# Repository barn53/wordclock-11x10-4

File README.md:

# wordclock-11x10-4
Wordclock project with 11x10 letter display + 4 minute identifier

# KiCad dependencies:

https://github.com/gerdmuller/barn53-kicad-library.git

https://github.com/Digi-Key/digikey-kicad-library.git

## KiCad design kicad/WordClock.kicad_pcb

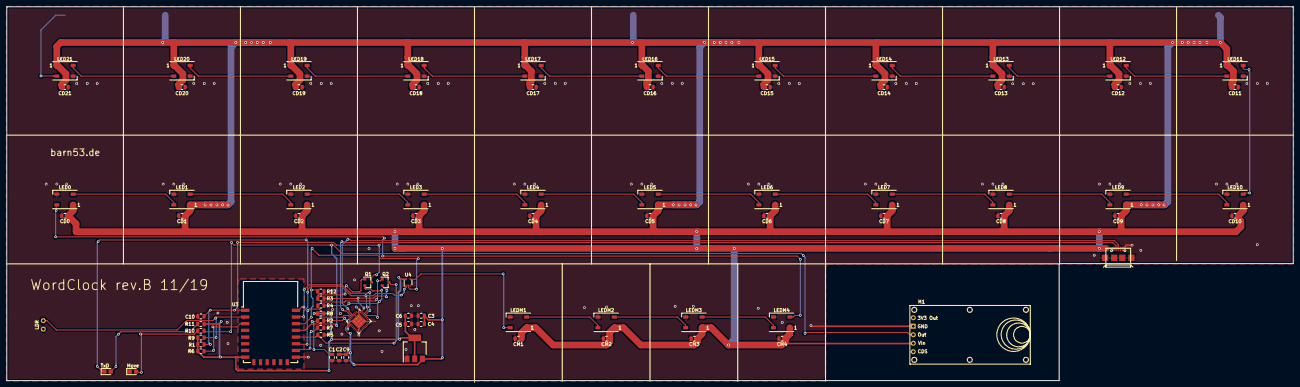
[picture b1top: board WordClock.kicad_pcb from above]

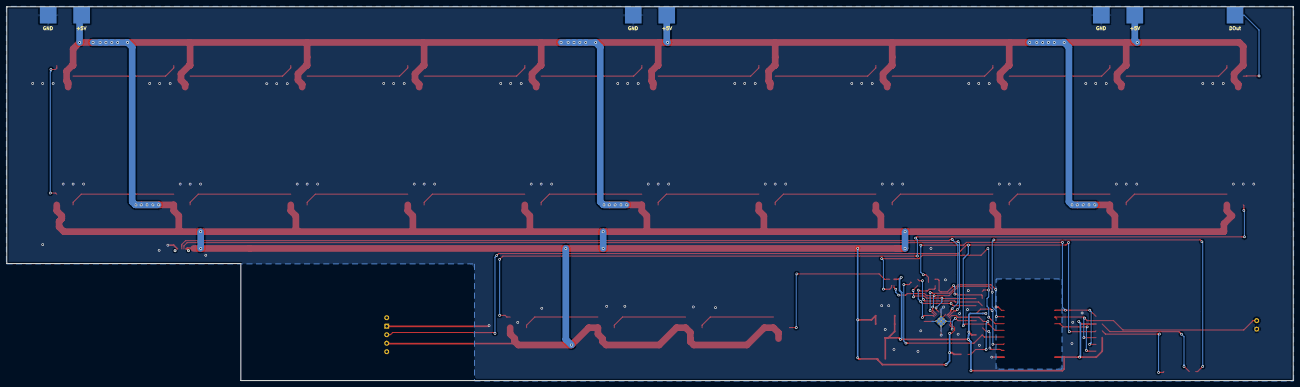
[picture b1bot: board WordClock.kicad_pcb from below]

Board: 2 copper layers, 384.8 x 111.8 mm, 90 parts (7 on the bottom side), 50 nets.

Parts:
C1, C4, C5, C9, C10: 100n; C_0805_2012Metric
C2: 4.7u; C_0805_2012Metric
C3, C6: 10u; C_0805_2012Metric
CD0, CD1, CD2, CD3, CD4, CD5, CD6, CD7, CD8, CD9, CD10, CD11, CD12, CD13, CD14, CD15, CD16, CD17, CD18, CD19, CD20, CD21: 100n; C_0805_2012Metric
CM1, CM2, CM3, CM4: 100n; C_0805_2012Metric
D1: Move; LED_0805_2012Metric_Castellated
D2: TxD; LED_0805_2012Metric_Castellated
J1: USB_B_Micro; MicroUSB_1
J2: LDR; ThroughHolePin1x2
J4: DOut; PCBSolderConnector
J5, J6, J7: +5V; PCBSolderConnector
J8, J9, J10: GND; PCBSolderConnector
LED0, LED1, LED2, LED3, LED4, LED5, LED6, LED7, LED8, LED9, LED10, LED11, LED12, LED13, LED14, LED15, LED16, LED17, LED18, LED19, LED20, LED21: WS2812B; LED_WS2812B_PLCC4_5.0x5.0mm_P3.2mm
LEDM1, LEDM2, LEDM3, LEDM4: WS2812B; LED_WS2812B_PLCC4_5.0x5.0mm_P3.2mm
M1: MicrowaveRadarSensorRCWL-0516
Q1, Q2: S8050_J3Y; SOT-23
R1, R2, R3, R4, R5, R6, R7, R8, R12: 10k; R_0805_2012Metric
R9: 220k; R_0805_2012Metric
R10, R11: 220; R_0805_2012Metric
U1: CP2102-GMR_NRND; QFN-28-1EP_5x5mm_P0.5mm_EP3.35x3.35mm_ThermalVias
U2: AMS1117-3.3; SOT-223-3_TabPin2
U3: ESP-12E
U4: 74AHC1G08; SOT-353_SC-70-5

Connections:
+3V3: C5.1, C6.1, R1.1, R5.1, R6.1, R8.1, R9.1, R11.1, U2.2, U3.8, U4.5
D+: J1.3, U1.4
D-: J1.2, U1.5
DIn: LEDM1.4, U4.4
DOUT: J4.1, LED21.2
DTR: Q2.2, R3.2, U1.28
GND: C1.2, C2.2, C3.2, C4.2, C5.2, C6.2, C9.2, C10.2, CD0.2, CD1.2, CD2.2, CD3.2, CD4.2, CD5.2, CD6.2, CD7.2, CD8.2, CD9.2, CD10.2, CD11.2, CD12.2, CD13.2, CD14.2, CD15.2, CD16.2, CD17.2, CD18.2, CD19.2, CD20.2, CD21.2, CM1.2, CM2.2, CM3.2, CM4.2, D1.1, J1.5, J1.6, J2.2, J8.1, J9.1, J10.1, LED0.3, LED1.3, LED2.3, LED3.3, LED4.3, LED5.3, LED6.3, LED7.3, LED8.3, LED9.3, LED10.3, LED11.3, LED12.3, LED13.3, LED14.3, LED15.3, LED16.3, LED17.3, LED18.3, LED19.3, LED20.3, LED21.3, LEDM1.3, LEDM2.3, LEDM3.3, LEDM4.3, M1.2, R7.2, R12.2, U1.3, U1.29, U2.1, U3.15, U4.3
GPIO0: Q2.3, R5.2, U3.18
GPIO5: R12.1, U3.20, U4.2
Move: M1.3, R10.1, U3.19
unnamed: D1.2, R10.2
unnamed: D2.2, R11.2
unnamed: J2.1, R9.2, U3.2
unnamed: LED0.2, LED1.4
unnamed: LED0.4, LEDM4.2
unnamed: LED1.2, LED2.4
unnamed: LED2.2, LED3.4
unnamed: LED3.2, LED4.4
unnamed: LED4.2, LED5.4
unnamed: LED5.2, LED6.4
unnamed: LED6.2, LED7.4
unnamed: LED7.2, LED8.4
unnamed: LED8.2, LED9.4
unnamed: LED10.2, LED11.4
unnamed: LED9.2, LED10.4
unnamed: LED11.2, LED12.4
unnamed: LED12.2, LED13.4
unnamed: LED13.2, LED14.4
unnamed: LED14.2, LED15.4
unnamed: LED15.2, LED16.4
unnamed: LED16.2, LED17.4
unnamed: LED17.2, LED18.4
unnamed: LED18.2, LED19.4
unnamed: LED19.2, LED20.4
unnamed: LED20.2, LED21.4
unnamed: LEDM1.2, LEDM2.4
unnamed: LEDM2.2, LEDM3.4
unnamed: LEDM3.2, LEDM4.4
unnamed: Q1.1, R3.1
unnamed: Q2.1, R4.1
unnamed: R2.1, U1.9
unnamed: R6.2, U3.3
unnamed: R7.1, U3.16
unnamed: R8.2, U3.17
RTS: Q1.2, R4.2, U1.24
Reset: C10.1, Q1.3, R1.2, U3.1
RxD: U1.25, U3.22
TxD: D2.1, U1.26, U3.21, U4.1
VBUS: C2.1, C3.1, C4.1, C9.1, CD0.1, CD1.1, CD2.1, CD3.1, CD4.1, CD5.1, CD6.1, CD7.1, CD8.1, CD9.1, CD10.1, CD11.1, CD12.1, CD13.1, CD14.1, CD15.1, CD16.1, CD17.1, CD18.1, CD19.1, CD20.1, CD21.1, CM1.1, CM2.1, CM3.1, CM4.1, J1.1, J5.1, J6.1, J7.1, LED0.1, LED1.1, LED2.1, LED3.1, LED4.1, LED5.1, LED6.1, LED7.1, LED8.1, LED9.1, LED10.1, LED11.1, LED12.1, LED13.1, LED14.1, LED15.1, LED16.1, LED17.1, LED18.1, LED19.1, LED20.1, LED21.1, LEDM1.1, LEDM2.1, LEDM3.1, LEDM4.1, M1.4, U1.7, U1.8, U2.3
VDD: C1.1, R2.2, U1.6

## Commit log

2019-10-29 initial project setup
2019-11-03 initial
2019-11-03 PCB routed
2019-11-03 added kicad gitignore
2019-11-04 updated pcb with new barn53-kicad path
2019-11-04 .gitignore
2019-11-04 added fp-info-cache to .gitignore
2019-11-04 added panel 2 with 11x10 LEDs
2019-11-04 C3+C6 as 0805 instead of 1206
2019-11-05 added LEDs, CP2102 45°
2019-11-08 added AND gate to disable WS2812 DIn when flashing
2019-11-10 pcb work
2019-11-11 minor
2019-11-12 added schematics as .pdf
2019-11-19 painful error!
    Q1 and Q2 had the wrong pins with footprint SO-23!!!!! Added new S8050_J3 Symbol in barn32-kicad library with correct pinning.
2019-11-19 Added missing pull down resistor
    Aaaaaargh!
2020-01-03 Added letter matrix 11x10+4 for 500mm size
2020-01-13 updated kicad structure
2020-05-26 working version
2020-05-29 pre-bitvector :-)
2020-09-02 new stuff
